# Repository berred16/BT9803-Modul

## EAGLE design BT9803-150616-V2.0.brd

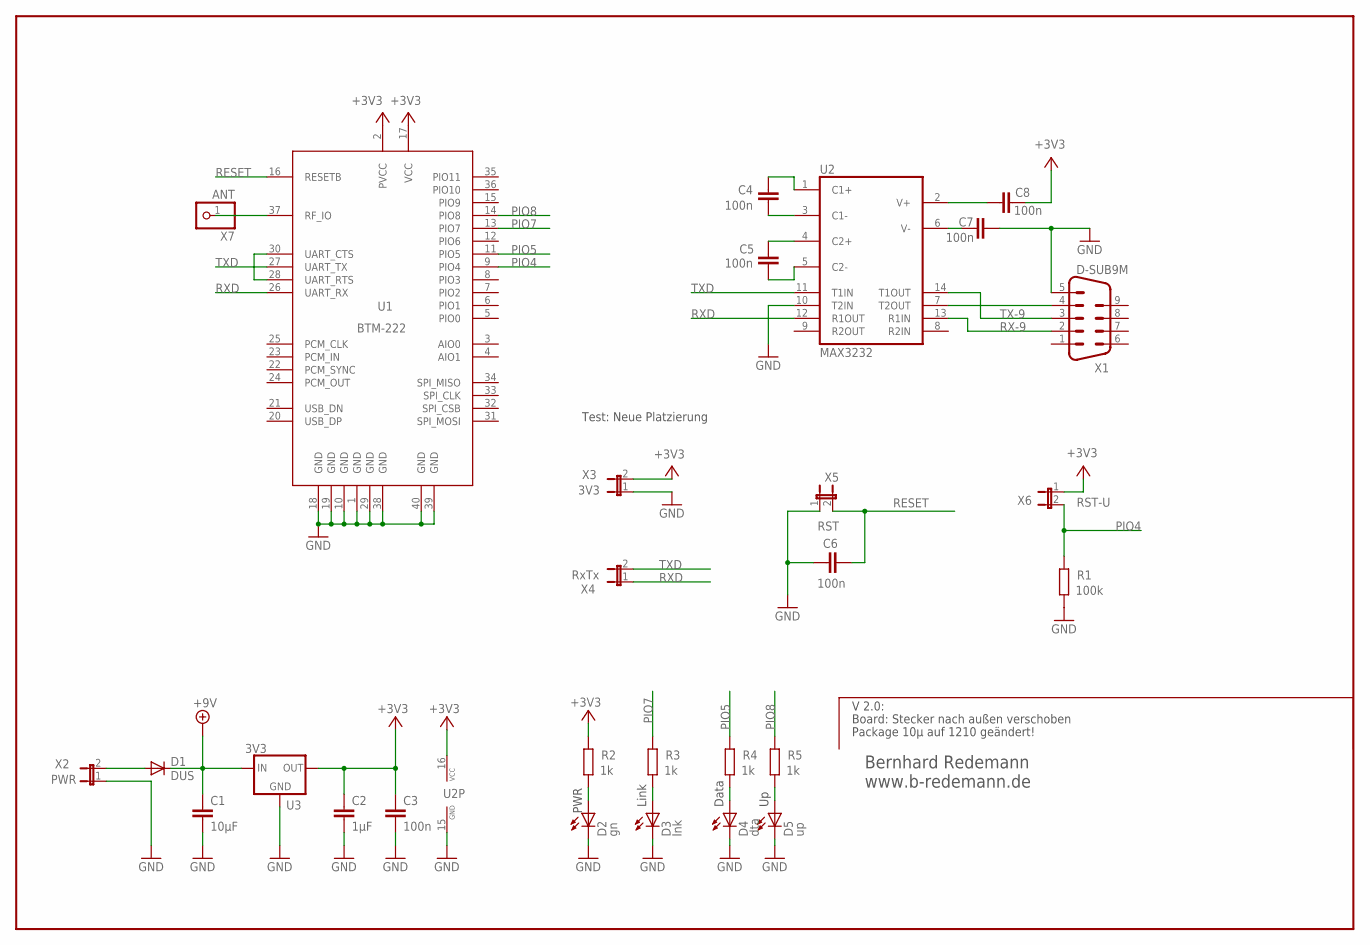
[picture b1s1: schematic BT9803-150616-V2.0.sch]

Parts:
C1: 10µF; C1210
C2: 1µF; C0805
C3, C4, C5, C6, C7, C8: 100n; C0805
D1: DUS; DO-214AC
D2: gn; CHIP-LED0805
D3: lnk; LED3MM
D4: dta; LED3MM
D5: up; LED3MM
R1: 100k; R0805
R2, R3, R4, R5: 1k; R0805
U1: BTM-222; 38-PIN15
U2: MAX3232; TSSOP16
U3: 3V3; SOT223
X1: D-SUB9M; M09D
X2: PWR; JP1
X3: 3V3; JP1
X4: RxTx; JP1
X5: RST; JP1
X6: RST-U; JP1
X7: ANT; 1X01

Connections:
+3V3: C2.1, C3.1, C8.1, R2.1, U1.2 (PVCC), U1.17 (VCC), U2.16 (VCC), U3.2 (OUT), X3.2, X6.1
+9V: C1.1, D1.C, U3.3 (IN)
DATA: D4.A, R4.2
GND: C1.2, C2.2, C3.2, C6.1, C7.1, D2.C, D3.K (C), D4.K (C), D5.K (C), R1.2, U1.1 (GND), U1.10 (GND), U1.18 (GND), U1.19 (GND), U1.29 (GND), U1.38 (GND), U1.39 (GND), U1.40 (GND), U2.10 (T2IN), U2.15 (GND), U3.1 (GND), X1.5, X2.1, X3.1, X5.1
LINK: D3.A, R3.2
unnamed: U2.7 (T2OUT), X1.4
unnamed: U1.28 (UART_RTS), U1.30 (UART_CTS)
unnamed: D1.A, X2.2
unnamed: C4.1, U2.3 (C1-)
unnamed: C5.2, U2.4 (C2+)
unnamed: C4.2, U2.1 (C1+)
unnamed: C5.1, U2.5 (C2-)
unnamed: C7.2, U2.6 (V-)
unnamed: C8.2, U2.2 (V+)
PIO4: R1.1, U1.9 (PIO4), X6.2
PIO5: R4.1, U1.11 (PIO5)
PIO7: R3.1, U1.13 (PIO7)
PIO8: R5.1, U1.14 (PIO8)
PWR: D2.A, R2.2
RESET: C6.2, U1.16 (RESETB), X5.2
RF-222: U1.37 (RF_IO), X7.1
RX-9: U2.13 (R1IN), X1.2
RXD: U1.26 (UART_RX), U2.12 (R1OUT), X4.1
TX-9: U2.14 (T1OUT), X1.3
TXD: U1.27 (UART_TX), U2.11 (T1IN), X4.2
UP: D5.A, R5.2

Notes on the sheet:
Bernhard Redemann www.b-redemann.de
Link
PWR
Data
Package 10µ auf 1210 geändert!
Board: Stecker nach außen verschoben
V 2.0:
Test: Neue Platzierung

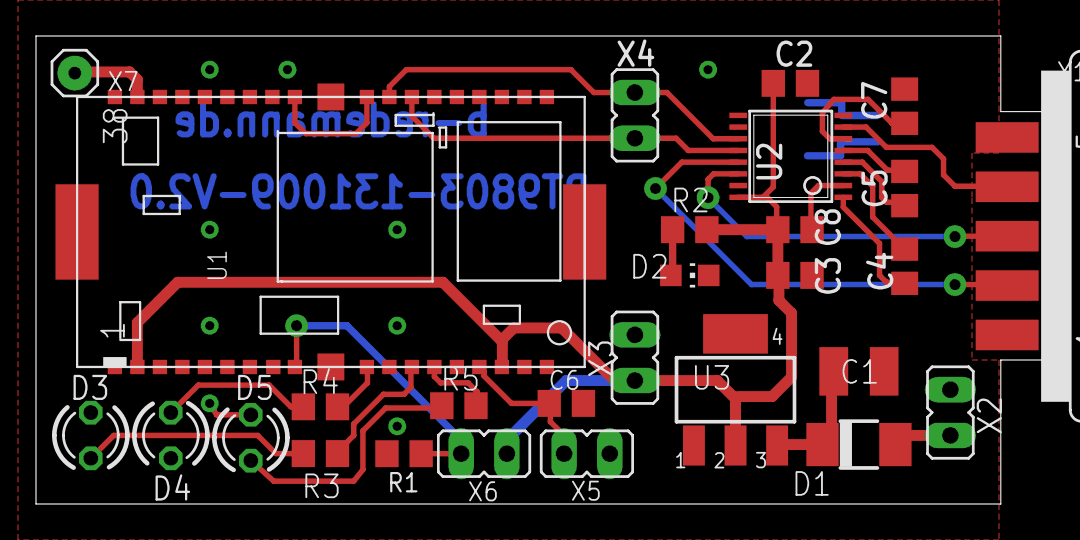
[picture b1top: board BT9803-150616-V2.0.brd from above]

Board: 2 copper layers, 56.0 x 26.0 mm, 28 parts (0 on the bottom side), 26 nets.
